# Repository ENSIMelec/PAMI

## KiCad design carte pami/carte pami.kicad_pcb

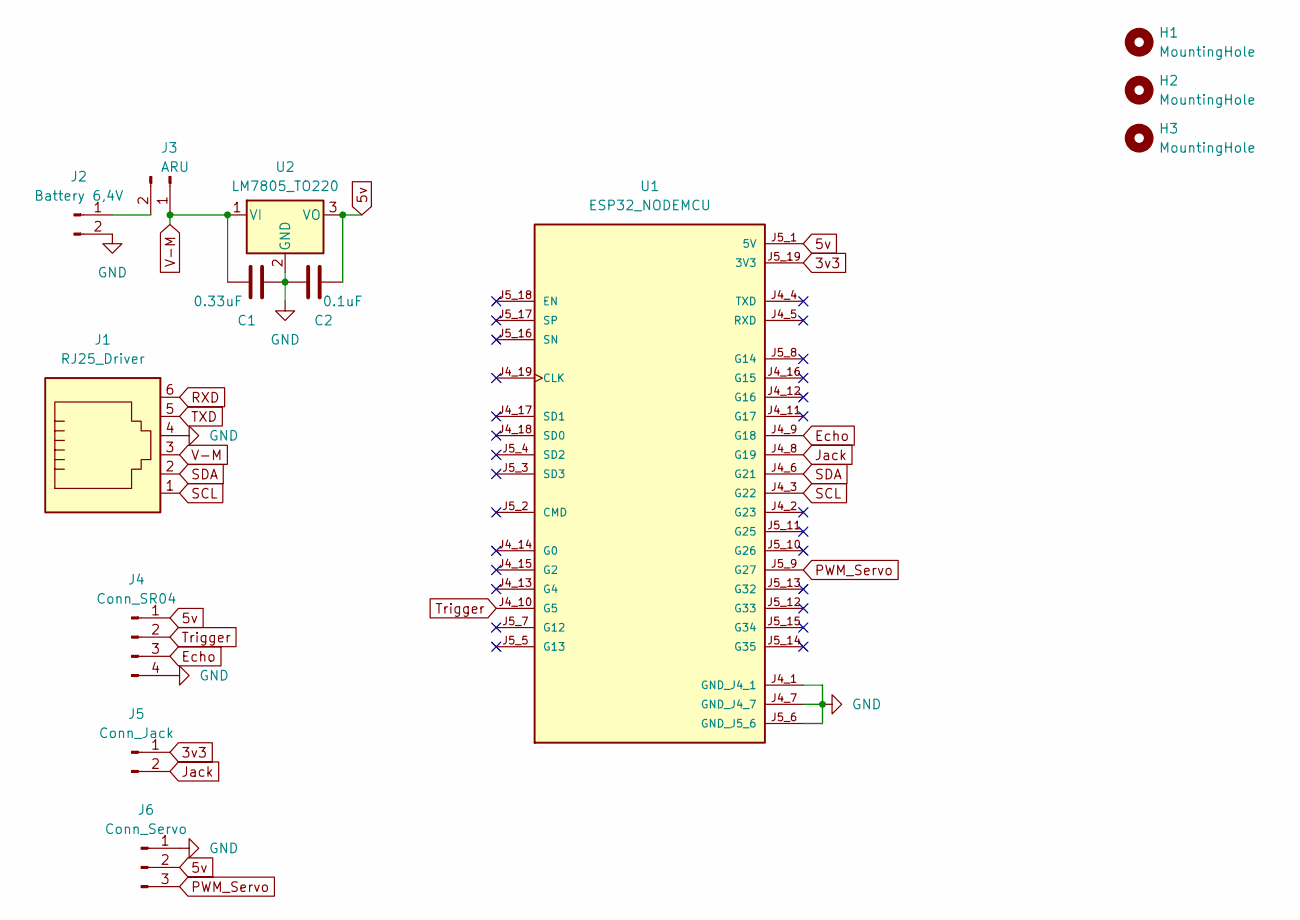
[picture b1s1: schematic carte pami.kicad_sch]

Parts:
C1: 0.33uF; C_Disc_D10.5mm_W5.0mm_P5.00mm
C2: 0.1uF; C_Disc_D10.5mm_W5.0mm_P5.00mm
H1, H2, H3: MountingHole; MountingHole_3.2mm_M3
J1: RJ25_Driver; Rj25
J2: Battery 6,4V; JST_XH_B2B-XH-A_1x02_P2.50mm_Vertical
J3: ARU; JST_XH_B2B-XH-A_1x02_P2.50mm_Vertical
J4: Conn_SR04; JST_PH_B4B-PH-K_1x04_P2.00mm_Vertical
J5: Conn_Jack; JST_PH_B2B-PH-K_1x02_P2.00mm_Vertical
J6: Conn_Servo; JST_PH_B3B-PH-K_1x03_P2.00mm_Vertical
U1: ESP32_NODEMCU; MODULE_ESP32_NODEMCU
U2: LM7805_TO220; TO-220-3_Vertical

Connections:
3v3: J5.1, U1.J5_19 (3V3)
5v: C2.2, J4.1, J6.2, U1.J5_1 (5V), U2.3 (VO)
Echo: J4.3, U1.J4_9 (G18)
GND: C1.2, C2.1, J1.4, J2.2, J4.4, J6.1, U1.J4_1 (GND_J4_1), U1.J4_7 (GND_J4_7), U1.J5_6 (GND_J5_6), U2.2 (GND)
Jack: J5.2, U1.J4_8 (G19)
unnamed: J2.1, J3.2
PWM_Servo: J6.3, U1.J5_9 (G27)
RXD: J1.6
SCL: J1.1, U1.J4_3 (G22)
SDA: J1.2, U1.J4_6 (G21)
TXD: J1.5
Trigger: J4.2, U1.J4_10 (G5)
V-M: C1.1, J1.3, J3.1, U2.1 (VI)

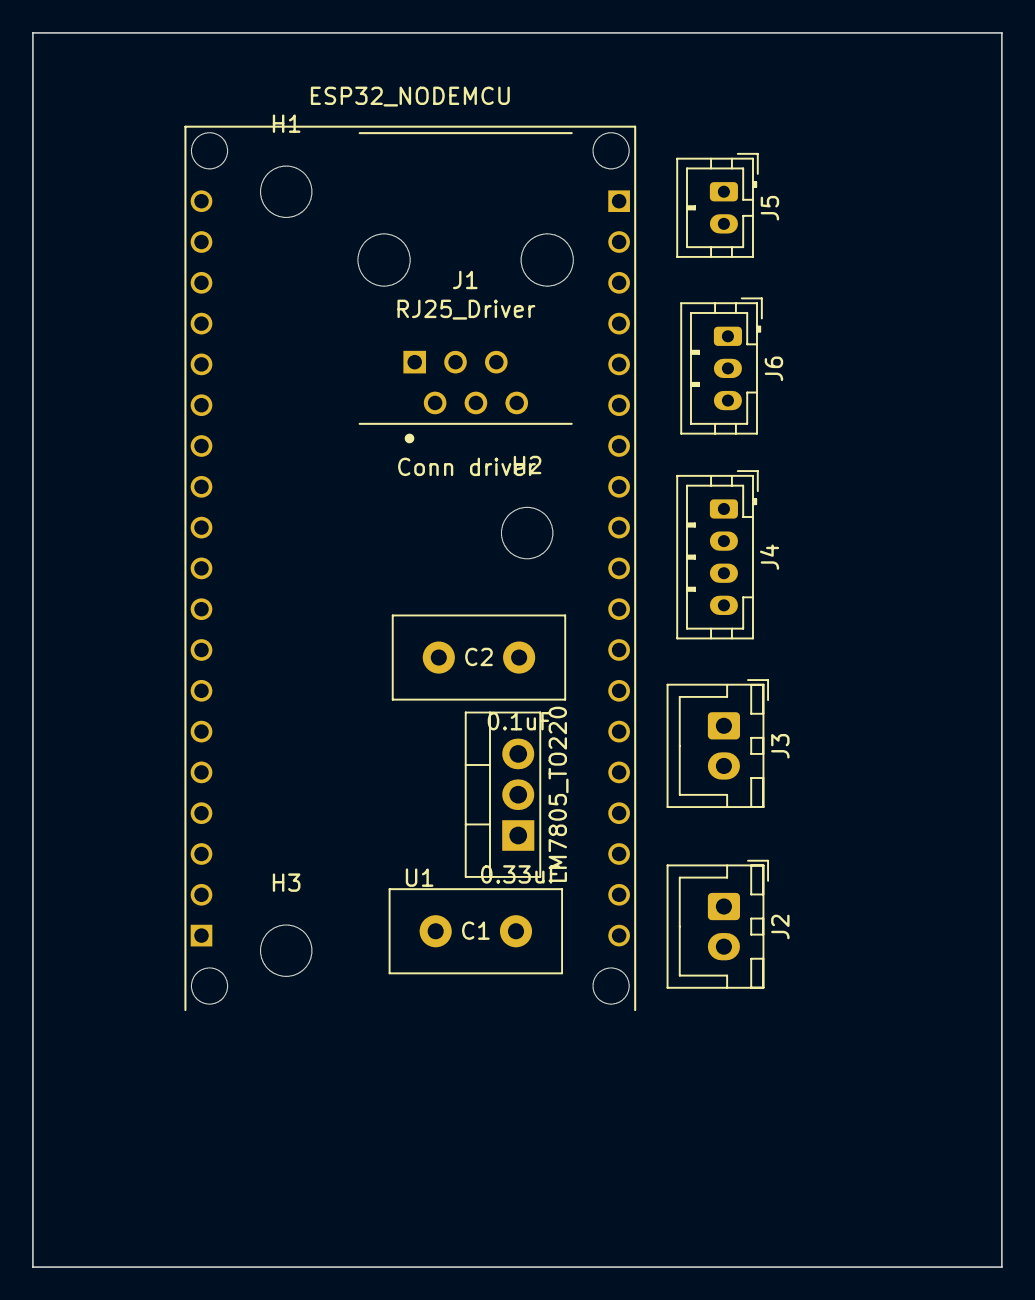
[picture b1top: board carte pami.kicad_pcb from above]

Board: 2 copper layers, 60.3 x 76.8 mm, 13 parts (0 on the bottom side), 11 nets.

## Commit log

2024-03-28 all files
2024-04-04 Baptiste ferme la
2024-04-18 Carte elec
2024-04-18 NAthan t nul
2024-05-02 le vrai code qui marche presque enfaite
2024-05-06 chore: Update interruption.h, main.h, and interruption.cpp
2024-05-06 feat: Update PID coefficients for left and right motors
2024-05-07 chore: Update PID coefficients for left and right motors
2024-05-07 chore: Update PAMI strategy functions for yellow and blue teams
2024-05-10 chore: Remove unused code files
